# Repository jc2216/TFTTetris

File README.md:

# TFTTetris
A 1.8" TFT powered by a Raspberry Pi Pico that can play the hit game Tetris. Control the position of the block by rotating the device, and rotate the block by pressing a button.

## Features
- 1.8" TFT display
- Raspberry Pi Pico
- MPU-6050 IMU
- Push Button
- Active Buzzer
- 3.7V LiPo Battery
- TP4056 USB-C Charger

## Schematic

- TFT is connected to Raspberry Pi Pico through a few pins. Capacitors are also connected to soak up current spikes when the screen redraws.
- Transistors + Resistors to safely power backlight, while also allowing firmware to turn it on/off.
- MPU-6050 connected to Raspberry Pi Pico to detect rotational motion. Push button also connected to the Pi.
- Buzzer requires transistor to get more current than what the Pi can supply. Resistor limits current to transistor to be safe.
- TPU-4056 Battery Pads are connected to the Battery Socket. TP4056 Output pads are connected to Slide Switch, which can turn on and off the system. Diode prevents power from flowing backwards.

## PCB

- Ground fill added, routed the PCB.
- Added neat little drawings for fun.
- Had to create space for the TFT screen at the end (because it can't go over the buzzer + switch), led to more pain.
- The battery, TPU-4056, MPU-6050, and TFT board will hang off of the PCB.

## Firmware
- Currently in progress
- Will be added soon

## BOM
| Item | Qty | Supplier | Cost/item | Total | Link |
|---|---|---|---|---|---|
| Tact push button | 1 | AliExpress | $0.96 | $0.96 | [Link](https://www.aliexpress.us/item/3256805859865632.html) |
| MPU6050 | 1 | AliExpress | $3.89 | $3.89 | [Link](https://www.aliexpress.us/item/3256812536361672.html) |
| Raspberry Pi Pico | 1 | AliExpress | $2.63 | $2.63 | [Link](https://www.aliexpress.us/item/3256805430865417.html) |
| 1.8" TFT | 1 | AliExpress | $2.97 | $2.97 | [Link](https://www.aliexpress.us/item/3256805953674718.html) |
| 3.7V 800 mAh LiPo | 1 | AliExpress | $1.09 | $1.09 | [Link](https://www.aliexpress.us/item/3256808535461122.html) |
| S8050 transistors | 1 | AliExpress | $2.64 | $2.64 | [Link](https://www.aliexpress.us/item/3256806624734473.html) |
| Slide switch | 1 | AliExpress | $1.11 | $1.11 | [Link](https://www.aliexpress.us/item/3256804214993913.html) |
| TP4056 | 1 | AliExpress | $1.10 | $1.10 | [Link](https://www.aliexpress.us/item/3256808491871337.html) |
| SS14 Schottky diode | 1 | AliExpress | $2.18 | $2.18 | [Link](https://www.aliexpress.us/w/wholesale-ss14-Schottky-diode.html) |
| AO3401A transistor | 1 | AliExpress | $2.10 | $2.10 | [Link](https://www.aliexpress.us/item/3256811832598213.html) |
| Molex PicoBlade | 1 | AliExpress | $2.25 | $2.25 | [Link](https://www.aliexpress.us/item/3256809135240230.html) |
| R1, 100 Ω resistor, 0805 | 1 | | | | |
| R2, 10 kΩ resistor, 0805 | 1 | | | | |
| R3, 1 kΩ resistor, 0805 | 1 | | | | |
| C1, 10 µF ceramic capacitor, 0805 | 1 | | | | |
| C2, 100 nF ceramic capacitor, 0805 | 1 | | | | |
| Active buzzer, 3 to 3.3 V | 1 | | | | |
| PCB | 1 | JLCPCB | $4.00 | $4.00 | [Link](https://jlcpcb.com) |
| Estimated shipping | 1 | | | $15.63 | |
| **Total** | | | | **$42.55** | |

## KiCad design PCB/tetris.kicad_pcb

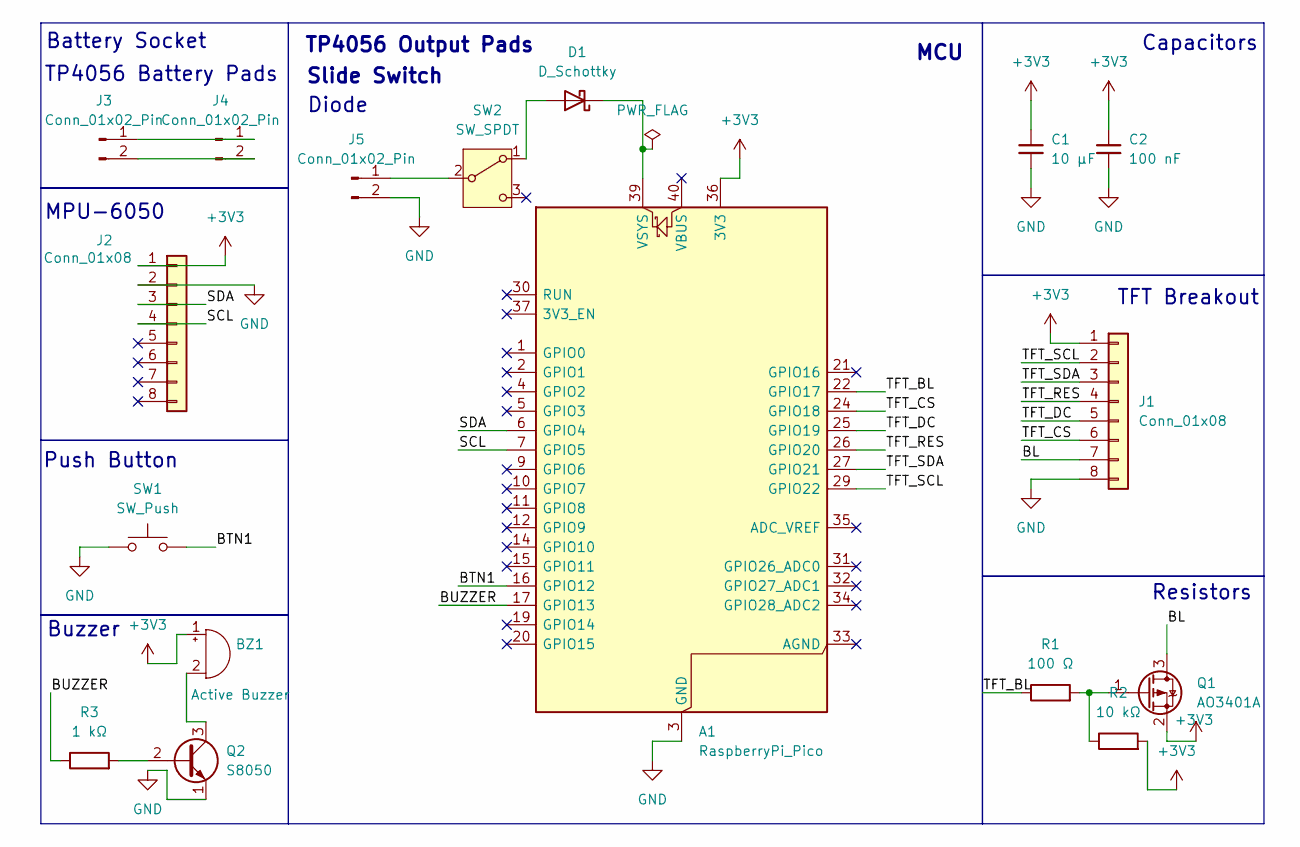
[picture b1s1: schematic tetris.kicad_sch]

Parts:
A1: RaspberryPi_Pico; RaspberryPi_Pico_Common_Unspecified
BZ1: Active Buzzer; Buzzer_12x9.5RM7.6
C1: 10 µF; C_0805_2012Metric
C2: 100 nF; C_0805_2012Metric
D1: D_Schottky; D_SMA
J1, J2: Conn_01x08; PinHeader_1x08_P2.54mm_Vertical
J3, J5: Conn_01x02_Pin; PinSocket_1x02_P2.54mm_Vertical
J4: Conn_01x02_Pin; Molex_PicoBlade_53261-0271_1x02-1MP_P1.25mm_Horizontal
Q1: AO3401A; SOT-23
Q2: S8050; TO-92_Inline
R1: 100 Ω; R_0805_2012Metric
R2: 10 kΩ; R_0805_2012Metric
R3: 1 kΩ; R_0805_2012Metric
SW1: SW_Push; SW_PUSH_6mm
SW2: SW_SPDT; PinHeader_1x03_P2.00mm_Vertical

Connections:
+3V3: A1.36 (3V3), BZ1.1 (+), C1.1, C2.1, J1.1, J2.1, Q1.2 (S), R2.2
/BL: J1.7, Q1.3 (D)
/BTN1: A1.16 (GPIO12), SW1.2
/BUZZER: A1.17 (GPIO13), R3.1
/SCL: A1.7 (GPIO5), J2.4
/SDA: A1.6 (GPIO4), J2.3
/TFT_BL: A1.22 (GPIO17), R1.1
/TFT_CS: A1.24 (GPIO18), J1.6
/TFT_DC: A1.25 (GPIO19), J1.5
/TFT_RES: A1.26 (GPIO20), J1.4
/TFT_SCL: A1.29 (GPIO22), J1.2
/TFT_SDA: A1.27 (GPIO21), J1.3
GND: A1.3 (GND), A1.8 (GND), A1.13 (GND), A1.18 (GND), A1.23 (GND), A1.28 (GND), A1.38 (GND), C1.2, C2.2, J1.8, J2.2, J5.2, Q2.1 (E), SW1.1
unnamed: A1.39 (VSYS), D1.1 (K)
unnamed: BZ1.2 (-), Q2.3 (C)
unnamed: D1.2 (A), SW2.1 (A)
unnamed: J3.1, J4.1
unnamed: J3.2, J4.2
unnamed: J5.1, SW2.2 (B)
unnamed: Q1.1 (G), R1.2, R2.1
unnamed: Q2.2 (B), R3.2

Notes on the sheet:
Capacitors
TP4056 Output Pads
TP4056 Battery Pads
MPU-6050
Push Button
TFT Breakout
MCU
Buzzer
Slide Switch
Diode
Battery Socket
Resistors

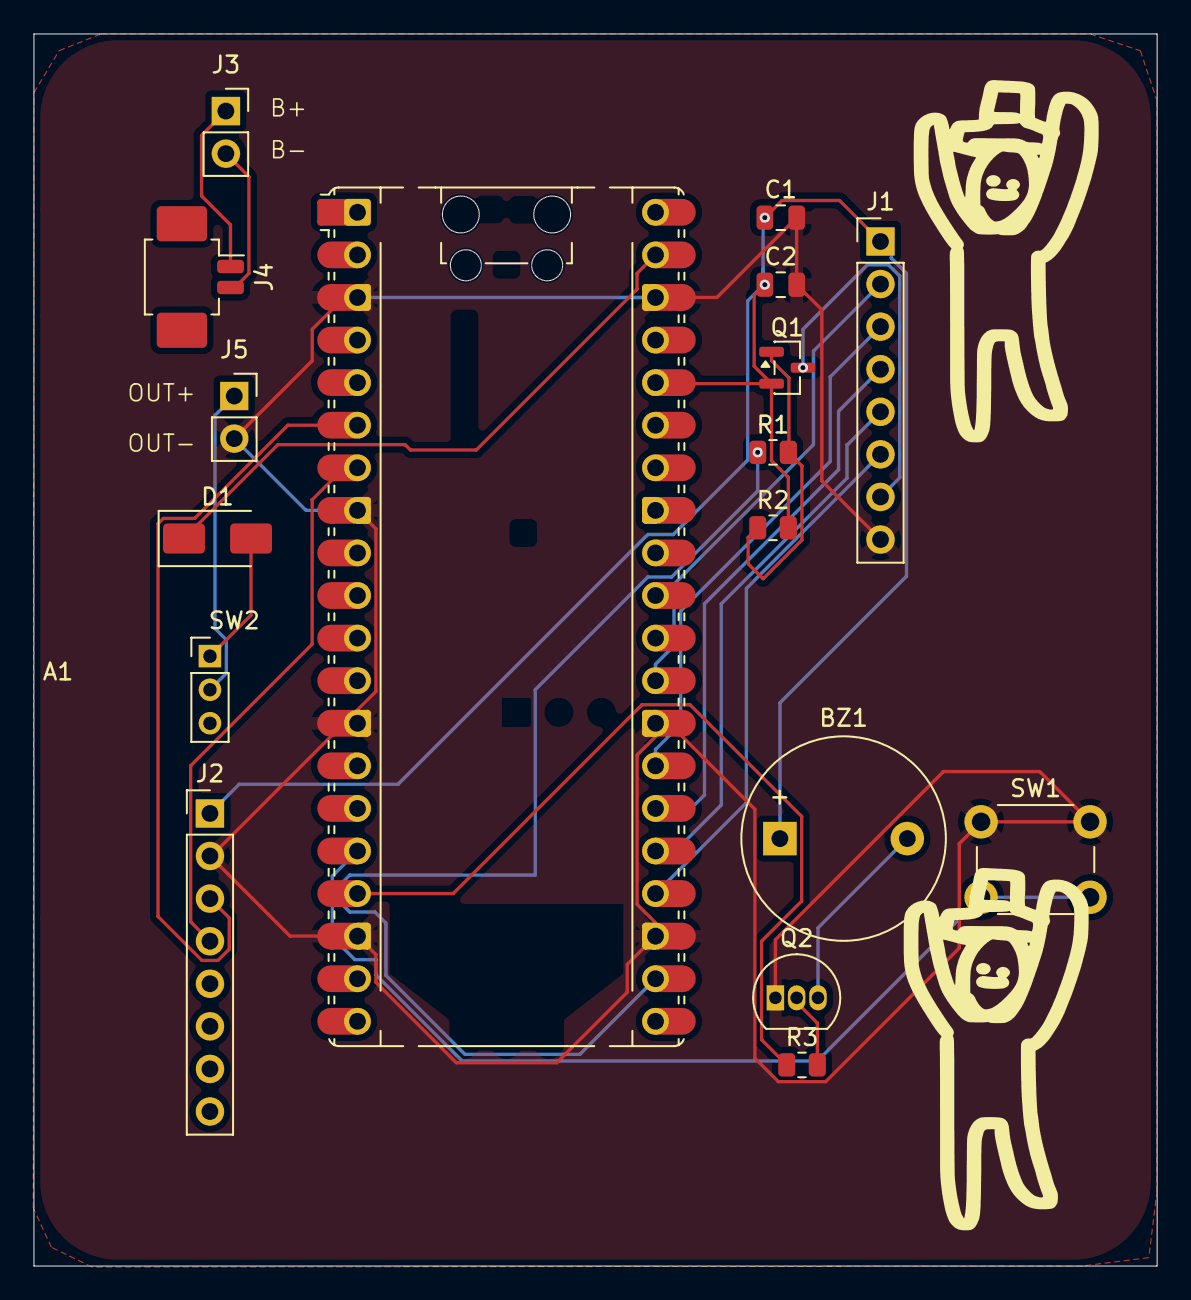
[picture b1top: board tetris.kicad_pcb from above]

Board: 2 copper layers, 67.0 x 73.5 mm, 17 parts (0 on the bottom side), 21 nets.
